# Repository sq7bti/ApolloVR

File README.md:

# ApolloVR
Apollo 1260 voltage regulator on steroids

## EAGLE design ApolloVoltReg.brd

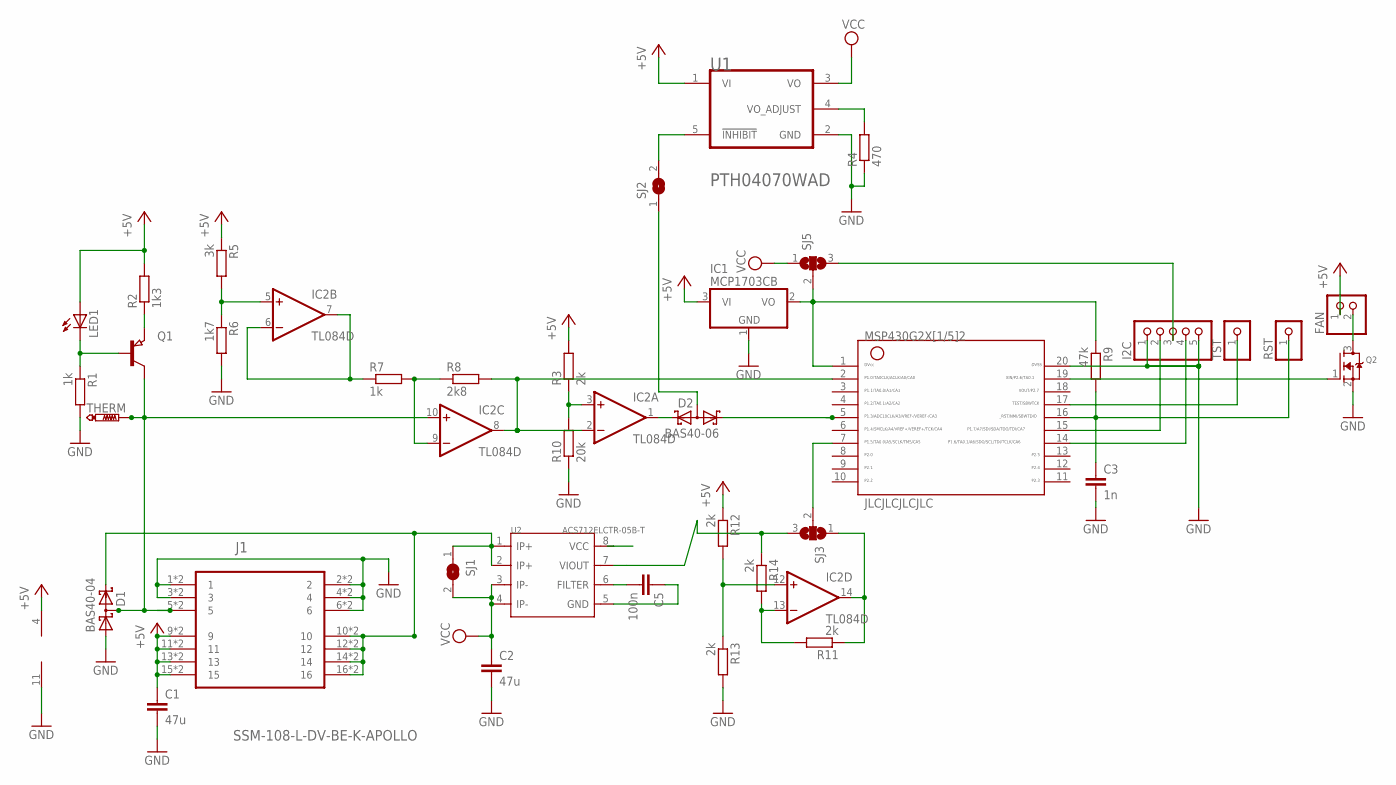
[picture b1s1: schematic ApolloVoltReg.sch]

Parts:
C1, C2: 47u; C1210
C3: 1n; C0603
C5: 100n; C0603
D1: BAS40-04; SOT23
D2: BAS40-06; SOT23
FAN: PINHD-1X2; 1X02
I2C: PINHD-1X5; 1X05
IC1: MCP1703CB; SOT23
IC2: TL084D; SO14
J1: SSM-108-L-DV-BE-K-APOLLO; SAMTEC_SSM-108-L-DV-BE-K-APOLLO
JLCJLCJLCJLC: G2X[1/5]2---N20; N20
LED1: LED3MM
Q1: PNP-TRANSISTOR_SOT23; SOT23
Q2: MOSFET-NREFLOW; SOT23
R1, R7: 1k; R0805
R2: 1k3; R0805
R3, R11, R12, R13: 2k; R0805
R4: 470; R0805
R5: 3k; R0805
R6: 1k7; R0805
R8: 2k8; R0805
R9: 47k; R0603
R10: 20k; R0805
R14: 2k; R0603
RST: PINHD-1X1CB; 1X01-CLEANBIG
SJ1: SJW
SJ2: SJ
SJ3, SJ5: SJ2W; SJ_2
THERM: PTR1B1,27; B1,27
TST: PINHD-1X1CB; 1X01-CLEANBIG
U1: TEXAS_INSTRUMENTS_PTH04070WADTEXAS_INSTRUMENTS_PT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; TEXAS_INSTRUMENTS_PTH04070WAD_0
U2: ACS712ELCTR-05B-T; SOIC8-1.27-5X4MM

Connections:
+5V: C1.1, FAN.1, IC1.3 (VI), IC2.4 (V+), J1.9, J1.11, J1.13, J1.15, J1.29 (9), J1.31 (11), J1.33 (13), J1.35 (15), LED1.A, R2.2, R3.2, R5.1, R12.1, U1.1 (VI), U2.8 (VCC)
/INHIBIT: SJ2.2, U1.5 (!INHIBIT!)
ACS_OUT: R14.1, SJ3.3, U2.7 (VIOUT)
CPU: D1.2 (C2), J1.10, J1.12, J1.14, J1.16, J1.30 (10), J1.32 (12), J1.34 (14), J1.36 (16), SJ1.1, U2.1 (IP+), U2.2 (IP+)
GND: C1.2, C2.2, C3.2, C5.1, D1.1 (A1), I2C.1, I2C.5, IC1.1 (GND), IC2.11 (V-), J1.1, J1.2, J1.3, J1.4, J1.6, J1.21 (1), J1.22 (2), J1.23 (3), J1.24 (4), J1.26 (6), JLCJLCJLCJLC.20, Q2.2 (S), R1.2, R4.1, R6.2, R10.1, R13.2, U1.2 (GND), U2.5 (GND)
unnamed: LED1.K (C), Q1.1 (B), R1.1
unnamed: Q1.2 (E), R2.1
unnamed: IC2.12 (+IN), R12.2, R13.1
unnamed: C5.2, U2.6 (FILTER)
unnamed: IC2.5 (+IN), R5.2, R6.1
unnamed: IC2.6 (-IN), IC2.7 (OUT), R7.1
unnamed: IC2.9 (-IN), R7.2, R8.1
unnamed: JLCJLCJLCJLC.19, Q2.1 (G)
unnamed: JLCJLCJLCJLC.17, TST.1
unnamed: IC2.3 (+IN), R3.1, R10.2
unnamed: D2.1 (K1), JLCJLCJLCJLC.5
unnamed: IC2.13 (-IN), R11.2, R14.2
unnamed: IC2.14 (OUT), R11.1, SJ3.1
unnamed: JLCJLCJLCJLC.7, SJ3.2
unnamed: IC1.2 (VO), JLCJLCJLCJLC.1, R9.1, SJ5.2
unnamed: D2.2 (K2), IC2.1 (OUT)
unnamed: D2.3 (AA), SJ2.1
unnamed: FAN.2, Q2.3 (D)
unnamed: I2C.3, SJ5.3
RST: C3.1, JLCJLCJLCJLC.16, R9.2, RST.1
SCL: I2C.4, JLCJLCJLCJLC.14
SDA: I2C.2, JLCJLCJLCJLC.15
TEMPSENS: IC2.2 (-IN), IC2.8 (OUT), JLCJLCJLCJLC.2, R8.2
THERM1: D1.3 (C1A2), IC2.10 (+IN), J1.5, J1.25 (5), Q1.3 (C), THERM.TP
VCC: C2.1, SJ1.2, SJ5.1, U1.3 (VO), U2.3 (IP-), U2.4 (IP-)
VO_ADJ: R4.2, U1.4 (VO_ADJUST)

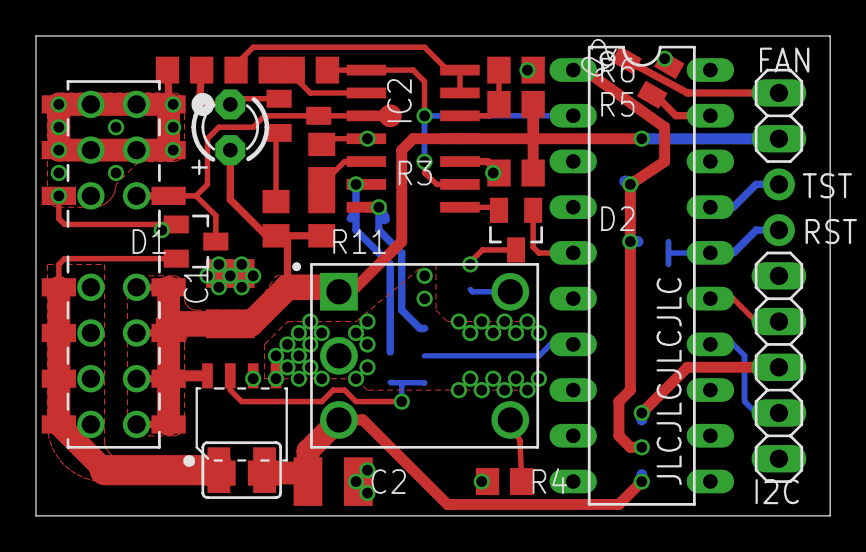
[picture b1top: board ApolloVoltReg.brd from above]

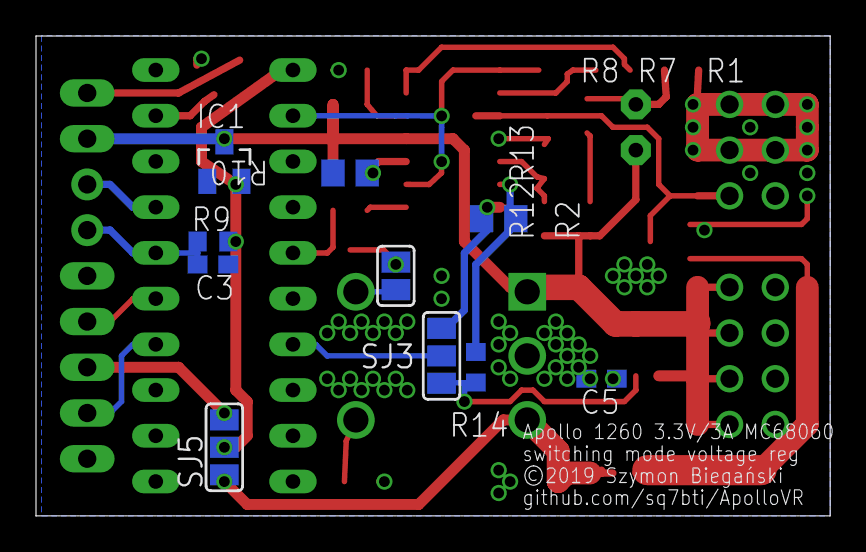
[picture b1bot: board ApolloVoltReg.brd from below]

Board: 2 copper layers, 44.1 x 26.7 mm, 38 parts (10 on the bottom side), 31 nets.

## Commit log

2019-09-07 PCB image
2019-09-08 pcb cleanup overtemp-shutdown (optional) gerber files
2019-09-08 replace opamp with TL084D
2019-09-08 add drawings
2019-09-08 add drawings to README
2019-09-08 widen high current traces
2019-09-10 gerber in archs
2019-11-01 adding pic

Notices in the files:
ApolloVoltReg.brd:
©2019 Szymon Biegański
